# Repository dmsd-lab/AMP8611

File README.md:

### AMP8611 - Integrated class AB Stereo Power Amplifier

Open hardware project under CERN-OHL-S v2 license
 
Amplifier combining a 2-channel input selector, 
PGA2311 digital volume control and 45W per-channel LM3886 output stages.  

Full documentation (description pdf, Kicad project schematic and PCB, Gerber files, BOM, STM32 firmware) is available in the repository.

**Key Specifications**:
- Input resistance: 10kΩ;  
- Nominal input voltage: 0.85Vrms; 
- Maximum output power: 2 x 45W RMS (1kHz sinusoidal, 4ohm load);  
- Bandwidth (-3dB): 20Hz – 90kHz;  
- Volume control: -80 to +12dB;  
- Dimensions: 240 x 265 x 65 mm (80 mm including feet).

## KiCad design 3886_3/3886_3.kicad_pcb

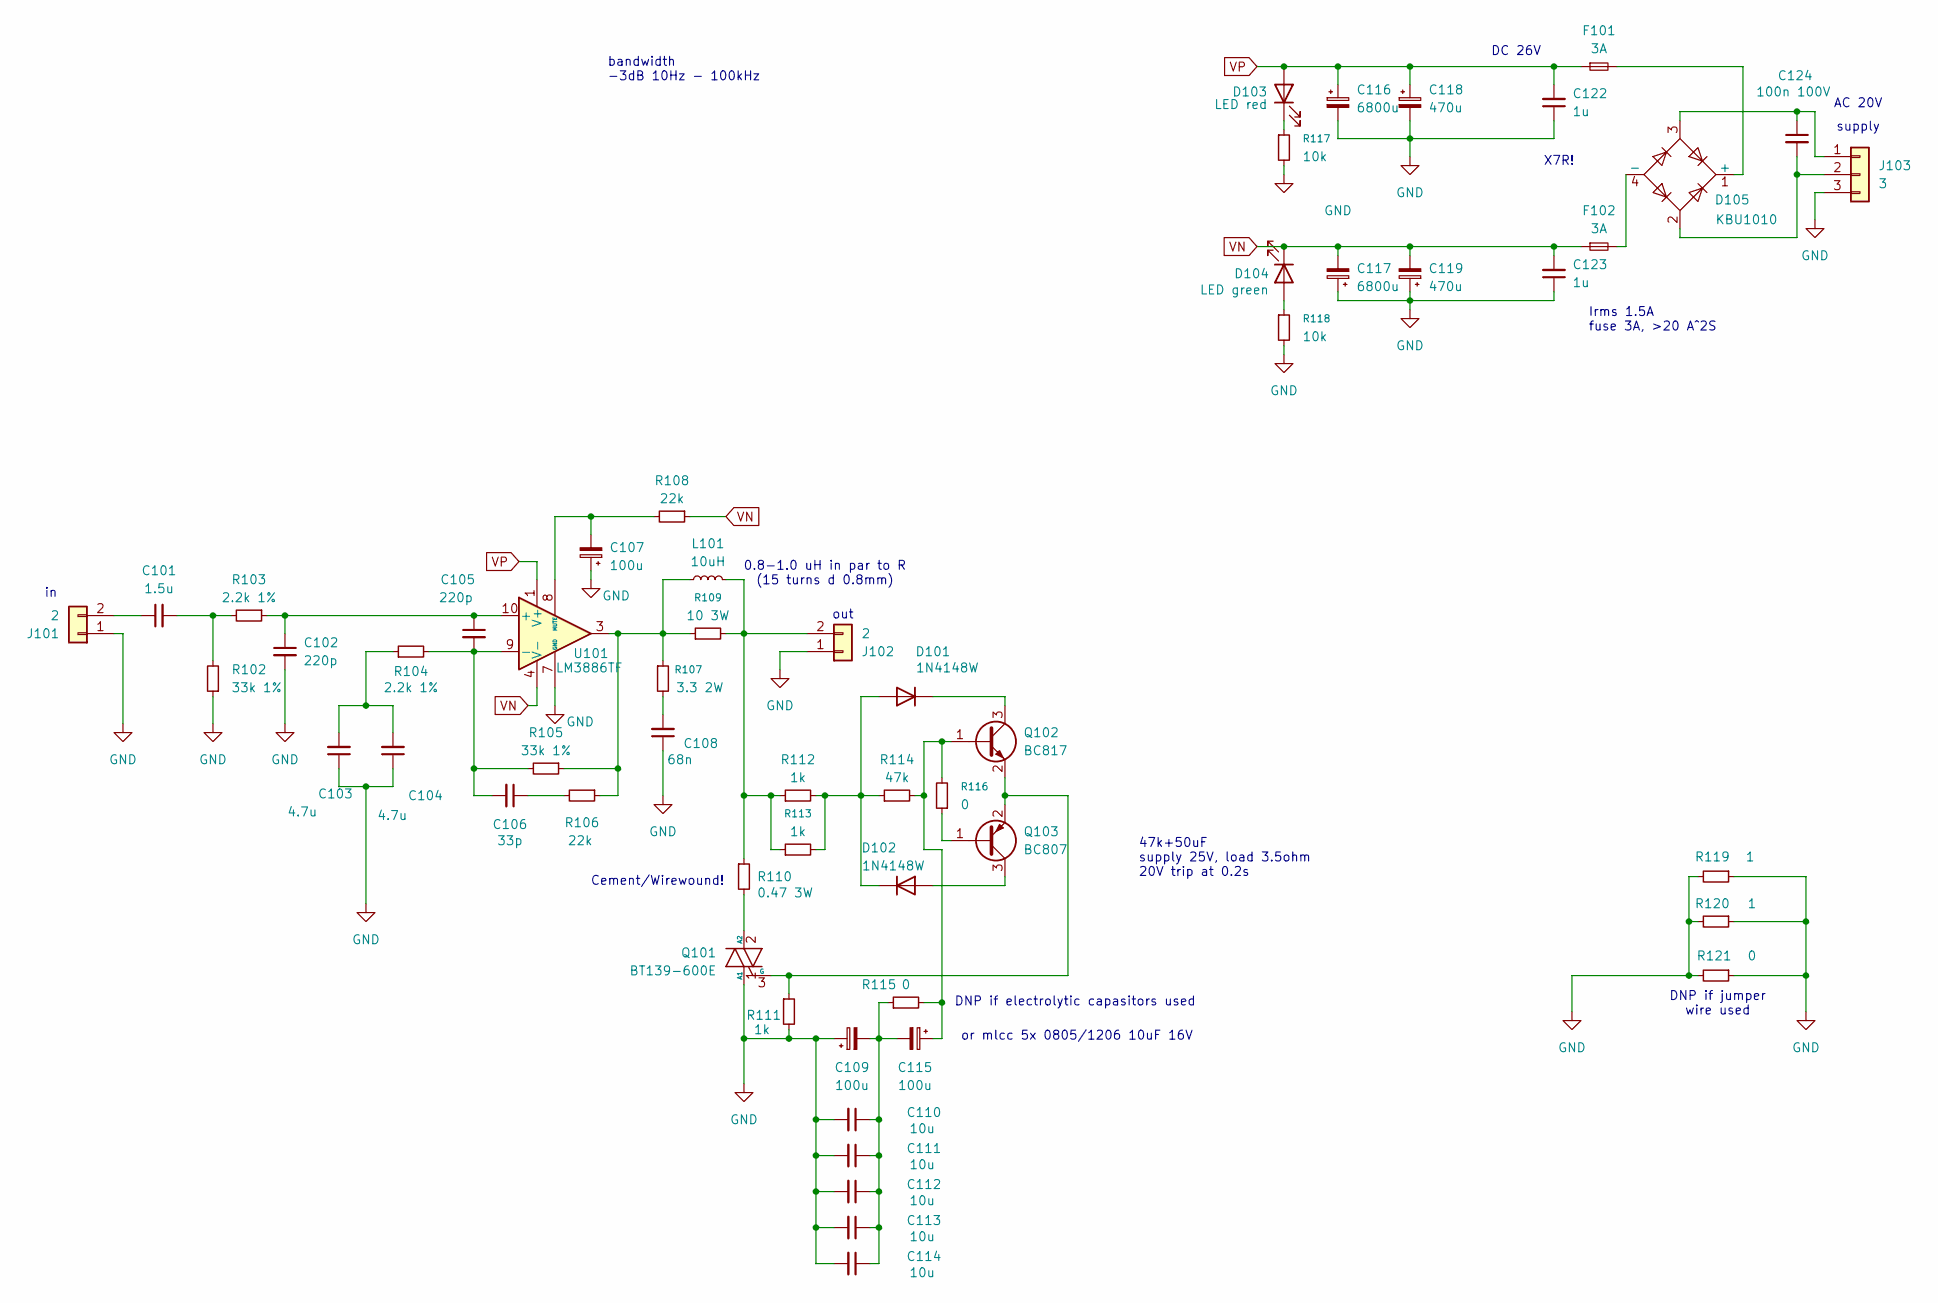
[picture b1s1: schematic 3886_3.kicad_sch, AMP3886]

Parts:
C101: 1.5u; C_Rect_L7.5mm_W6.5mm_P5.00mm
C102: 220p; C_1206_3216Metric_Pad1.33x1.80mm_HandSolder
C103, C104: 4.7u; C_Rect_L31.5mm_W13.0mm_P27.50mm_MKS4
C105: 220p; C_Rect_L7.0mm_W2.5mm_P5.00mm
C106: 33p; C_1206_3216Metric_Pad1.33x1.80mm_HandSolder
C107, C109, C115: 100u; CP_Radial_D6.3mm_P2.50mm
C108: 68n; C_Rect_L7.0mm_W3.5mm_P5.00mm
C110, C111, C112, C113, C114: 10u; C_1206_3216Metric_Pad1.33x1.80mm_HandSolder
C116, C117: 6800u; CP_Radial_D18.0mm_P7.50mm
C118, C119: 470u; CP_Radial_D10.0mm_P5.00mm
C122, C123: 1u; C_1206_3216Metric_Pad1.33x1.80mm_HandSolder
C124: 100n 100V; C_1206_3216Metric_Pad1.33x1.80mm_HandSolder
D101, D102: 1N4148W; D_MELF-RM10_Universal_Handsoldering
D103: LED red; LED_D5.0mm
D104: LED green; LED_D5.0mm
D105: KBU1010; Diode_Bridge_Vishay_KBU
F101, F102: 3A; Fuseholder_Cylinder-5x20mm_Stelvio-Kontek_PTF78_Horizontal_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
J101, J102: 2; PhoenixContact_MCV_1,5_2-G-3.81_1x02_P3.81mm_Vertical
J103: 3; PhoenixContact_MCV_1,5_3-G-5.08_1x03_P5.08mm_Vertical
L101: 10uH
Q101: BT139-600E; TO-220-3_Vertical
Q102: BC817; SOT-23_Handsoldering
Q103: BC807; SOT-23_Handsoldering
R102, R105: 33k 1%; R_Axial_DIN0207_L6.3mm_D2.5mm_P10.16mm_Horizontal
R103, R104: 2.2k 1%; R_Axial_DIN0207_L6.3mm_D2.5mm_P10.16mm_Horizontal
R106, R108: 22k; R_1206_3216Metric_Pad1.30x1.75mm_HandSolder
R107: 3.3 2W; R_Axial_DIN0614_L14.3mm_D5.7mm_P25.40mm_Horizontal
R109: 10 3W; R_Axial_DIN0922_L20.0mm_D9.0mm_P30.48mm_Horizontal
R110: 0.47 3W; R_Axial_Power_L25.0mm_W9.0mm_P7.62mm_Vertical
R111, R112, R113: 1k; R_1206_3216Metric_Pad1.30x1.75mm_HandSolder
R114: 47k; R_1206_3216Metric_Pad1.30x1.75mm_HandSolder
R115, R116: 0; R_1206_3216Metric_Pad1.30x1.75mm_HandSolder
R117, R118: 10k; R_1206_3216Metric_Pad1.30x1.75mm_HandSolder
R119, R120: 1; R_1206_3216Metric_Pad1.30x1.75mm_HandSolder
R121: 0; R_2512_6332Metric_Pad1.40x3.35mm_HandSolder
U101: LM3886TF; TO-220-11_P3.4x5.08mm_StaggerOdd_Lead4.58mm_Vertical

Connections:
GND: C102.2, C103.1, C104.1, C107.1, C108.1, C109.1, C110.2, C111.2, C112.2, C113.2, C114.2, C116.2, C117.1, C118.2, C119.1, C122.1, C123.1, J101.1, J102.1, J103.3, Q101.1 (A1), R102.1, R111.2, R117.2, R118.2, R119.1, R119.2, R120.1, R120.2, R121.1, R121.2, U101.7 (GND)
unnamed: C101.2, R102.2, R103.2
unnamed: C103.2, C104.2, R104.1
unnamed: C106.1, R106.2
unnamed: C108.2, R107.2
unnamed: C109.2, C110.1, C111.1, C112.1, C113.1, C114.1, C115.2, R115.1
unnamed: D101.2 (A), D102.1 (K), R112.2, R113.2, R114.1
unnamed: D101.1 (K), Q102.3 (C)
unnamed: D102.2 (A), Q103.3 (C)
unnamed: D103.1 (K), R117.1
unnamed: D104.2 (A), R118.1
unnamed: D105.1 (+), F101.2
unnamed: D105.4 (-), F102.2
unnamed: C101.1, J101.2
unnamed: J102.2, L101.2, R109.2, R110.1, R112.1, R113.1
unnamed: C124.1, D105.3, J103.1
unnamed: C124.2, D105.2, J103.2
unnamed: Q101.2 (A2), R110.2
unnamed: Q101.3 (G), Q102.2 (E), Q103.2 (E), R111.1
unnamed: C115.1, Q102.1 (B), R114.2, R115.2, R116.2
unnamed: Q103.1 (B), R116.1
unnamed: L101.1, R105.1, R106.1, R107.1, R109.1, U101.3
unnamed: C102.1, C105.1, R103.1, U101.10 (+)
unnamed: C105.2, C106.2, R104.2, R105.2, U101.9 (-)
unnamed: C107.2, R108.2, U101.8 (MUTE)
VN: C117.2, C119.2, C123.2, D104.1 (K), F102.1, R108.1, U101.4 (V-)
VP: C116.1, C118.1, C122.2, D103.2 (A), F101.1, U101.1 (V+), U101.5 (V+)

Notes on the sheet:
DC 26V
supply
X7R!
bandwidth -3dB 10Hz - 100kHz
47k+50uF supply 25V, load 3.5ohm 20V trip at 0.2s
DNP if electrolytic capasitors used
or mlcc 5x 0805/1206 10uF 16V
Irms 1.5A fuse 3A, >20 A^2S
AC 20V
out
0.8-1.0 uH in par to R (15 turns d 0.8mm)
Cement/Wirewound!
DNP if jumper wire used

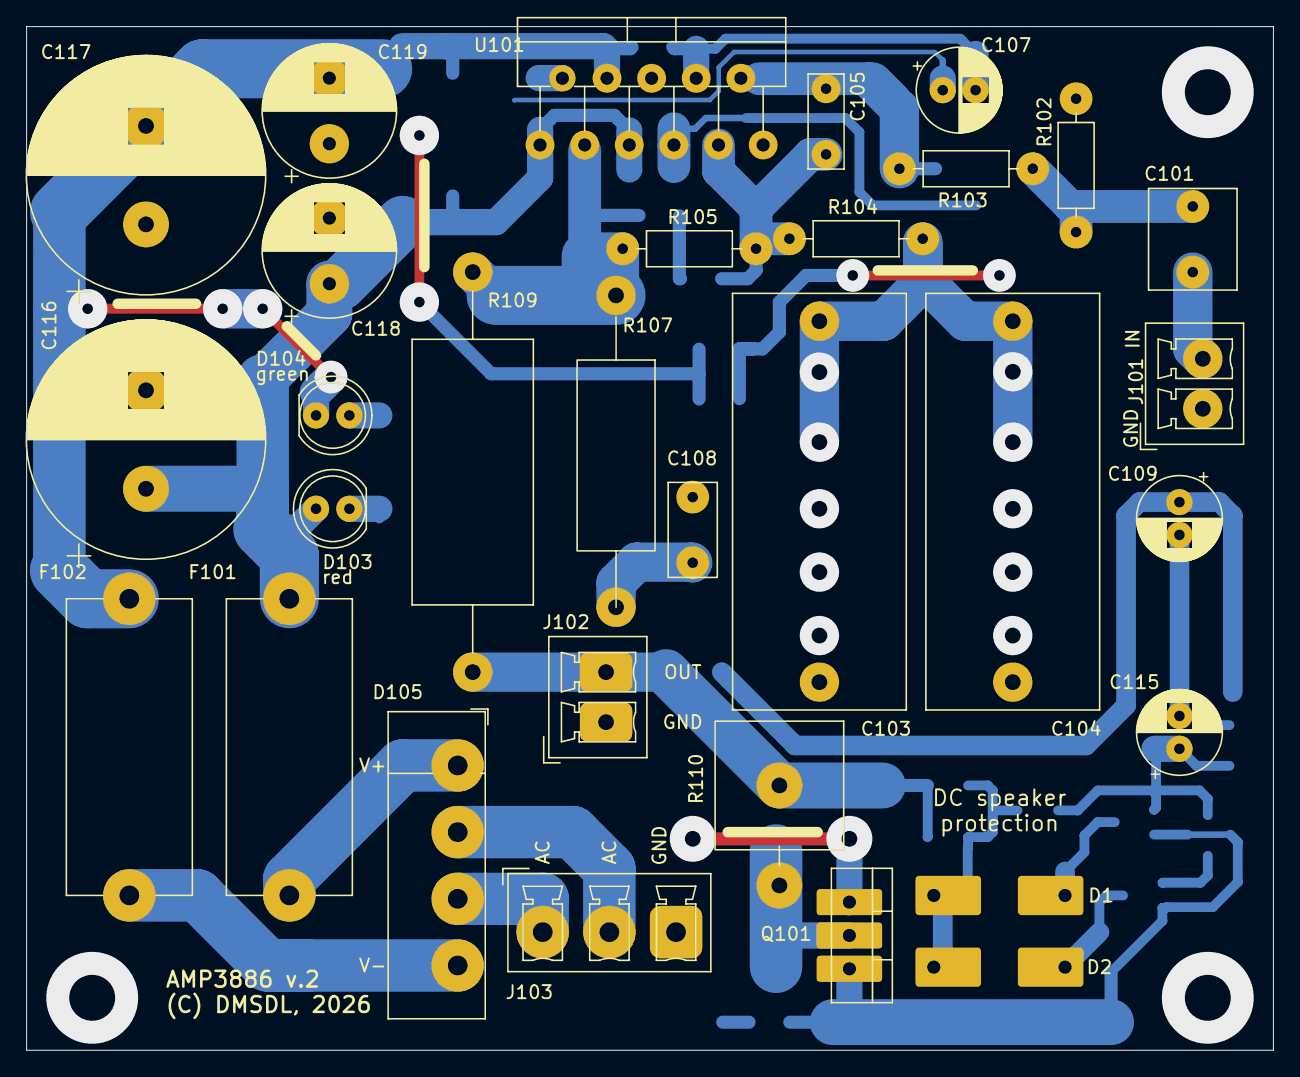
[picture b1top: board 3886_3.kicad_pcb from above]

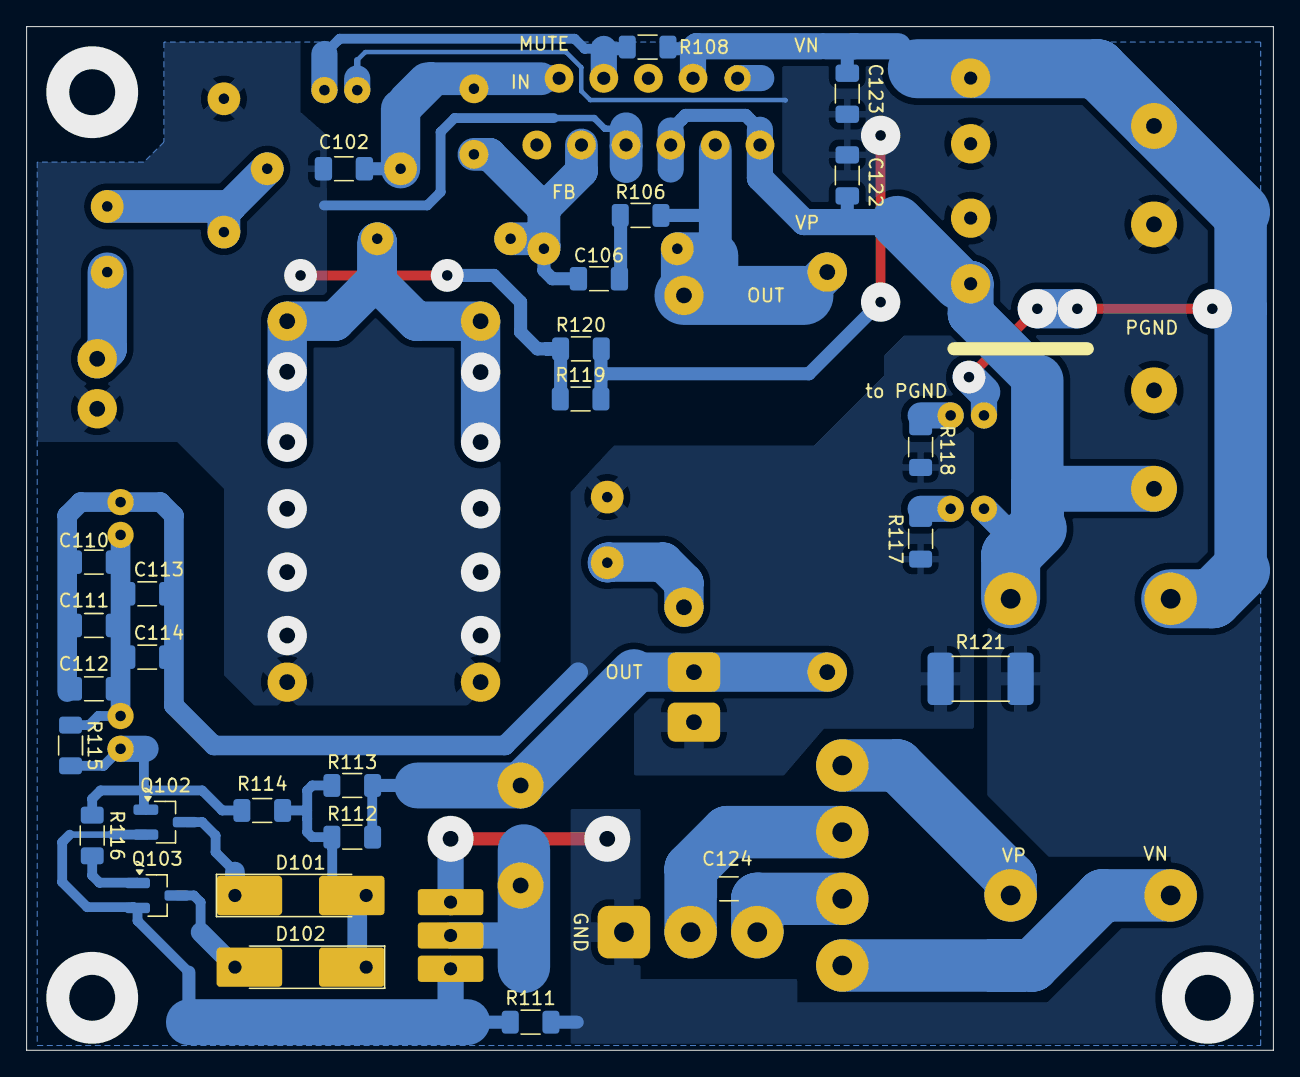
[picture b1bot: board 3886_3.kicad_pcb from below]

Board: 2 copper layers, 95.0 x 78.0 mm, 56 parts (27 on the bottom side), 27 nets.

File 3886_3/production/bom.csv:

Designator,Footprint,Quantity,Value,LCSC Part #
C101,C_Rect_L7.5mm_W6.5mm_P5.00mm,1,1.5u,
C102,1206,1,220p,
"C103, C104",C_Rect_L31.5mm_W13.0mm_P27.50mm_MKS4,2,4.7u,
C105,C_Rect_L7.0mm_W2.5mm_P5.00mm,1,220p,
C106,1206,1,33p,
"C107, C109, C115",CP_Radial_D6.3mm_P2.50mm,3,100u,
C108,C_Rect_L7.0mm_W3.5mm_P5.00mm,1,68n,
"C110, C111, C112, C113, C114",1206,5,10u,
"C116, C117",CP_Radial_D18.0mm_P7.50mm,2,6800u,
"C118, C119",CP_Radial_D10.0mm_P5.00mm,2,470u,
"C122, C123",1206,2,1u,
C124,1206,1,100n 100V,
"D101, D102",D_MELF-RM10_Universal_Handsoldering,2,1N4148W,
D103,LED_D5.0mm,1,LED red,
D104,LED_D5.0mm,1,LED green,
D105,Diode_Bridge_Vishay_KBU,1,KBU1010,
"F101, F102",Fuseholder_Cylinder-5x20mm_Stelvio-Kontek_PTF78_Horizontal_Open,2,3A,
"J101, J102","PhoenixContact_MCV_1,5_2-G-3.81_1x02_P3.81mm_Vertical",2,2,
J103,"PhoenixContact_MCV_1,5_3-G-5.08_1x03_P5.08mm_Vertical",1,3,
Q101,TO-220-3_Vertical,1,BT139-600E,
Q102,SOT-23_Handsoldering,1,BC817,
Q103,SOT-23_Handsoldering,1,BC807,
"R102, R105",R_Axial_DIN0207_L6.3mm_D2.5mm_P10.16mm_Horizontal,2,33k 1%,
"R103, R104",R_Axial_DIN0207_L6.3mm_D2.5mm_P10.16mm_Horizontal,2,2.2k 1%,
"R106, R108",1206,2,22k,
R107,R_Axial_DIN0614_L14.3mm_D5.7mm_P25.40mm_Horizontal,1,3.3 2W,
R109,R_Axial_DIN0922_L20.0mm_D9.0mm_P30.48mm_Horizontal,1,10 3W,
R110,R_Axial_Power_L25.0mm_W9.0mm_P7.62mm_Vertical,1,0.47 3W,
"R111, R112, R113",1206,3,1k,
R114,1206,1,47k,
"R115, R116",1206,2,0,
"R117, R118",1206,2,10k,
"R119, R120",1206,2,1,
R121,2512,1,0,
U101,TO-220-11_P3.4x5.08mm_StaggerOdd_Lead4.58mm_Vertical,1,LM3886TF,

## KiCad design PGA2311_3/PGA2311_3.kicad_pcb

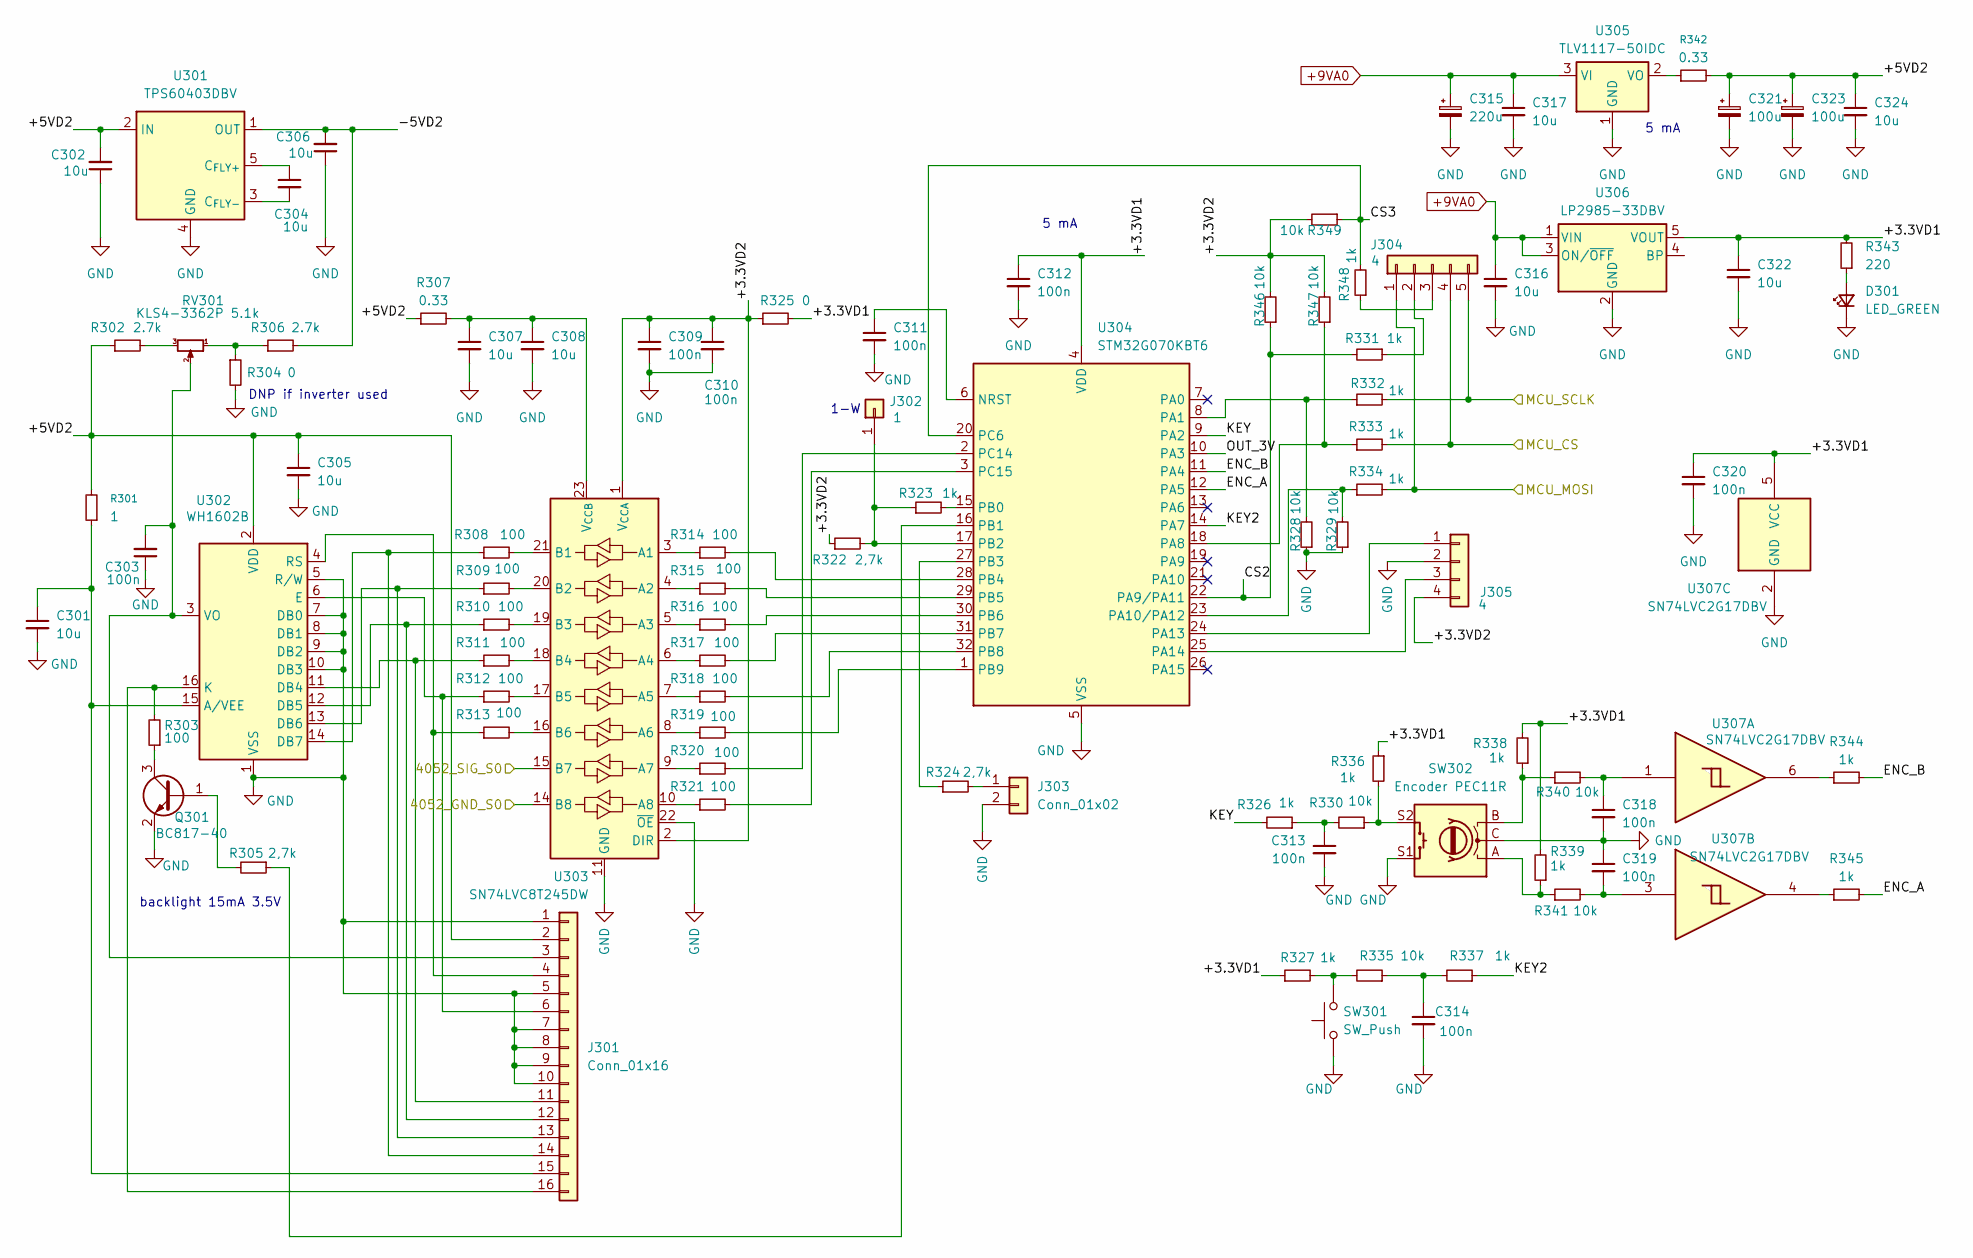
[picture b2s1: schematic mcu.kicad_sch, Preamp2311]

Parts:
C301, C302, C304, C305, C306, C307, C308, C316, C317, C322, C324: 10u; C_0805_2012Metric_Pad1.18x1.45mm_HandSolder
C303, C309, C310, C311, C312, C313, C314, C318, C319, C320: 100n; C_0805_2012Metric_Pad1.18x1.45mm_HandSolder
C315: 220u; CP_Radial_D8.0mm_P3.50mm
C321, C323: 100u; CP_Radial_D6.3mm_P2.50mm
D301: LED_GREEN; LED_D3.0mm
J301: Conn_01x16; PinSocket_1x16_P2.54mm_Horizontal
J302: 1; PinHeader_1x01_P2.54mm_Vertical
J303: Conn_01x02; PinHeader_1x02_P2.54mm_Vertical
J304: 4; PinHeader_1x05_P2.54mm_Vertical
J305: 4; PinHeader_1x04_P2.54mm_Vertical
Q301: BC817-40; SOT-23_Handsoldering
R301: 1; R_1206_3216Metric_Pad1.30x1.75mm_HandSolder
R302, R306: 2.7k; R_0805_2012Metric_Pad1.20x1.40mm_HandSolder
R303: 100; R_1206_3216Metric_Pad1.30x1.75mm_HandSolder
R304, R325: 0; R_0805_2012Metric_Pad1.20x1.40mm_HandSolder
R305, R322, R324: 2,7k; R_0805_2012Metric_Pad1.20x1.40mm_HandSolder
R307, R342: 0.33; R_0805_2012Metric_Pad1.20x1.40mm_HandSolder
R308, R309, R310, R311, R312, R313, R314, R315, R316, R317, R318, R319, R320, R321: 100; R_0805_2012Metric_Pad1.20x1.40mm_HandSolder
R323, R326, R327, R331, R332, R333, R334, R336, R337, R338, R339, R344, R345, R348: 1k; R_0805_2012Metric_Pad1.20x1.40mm_HandSolder
R328, R329, R330, R335, R340, R341, R346, R347, R349: 10k; R_0805_2012Metric_Pad1.20x1.40mm_HandSolder
R343: 220; R_0805_2012Metric_Pad1.20x1.40mm_HandSolder
RV301: KLS4-3362P 5.1k; Potentiometer_Vishay_T73YP_Vertical
SW301: SW_Push; SW_PUSH-12mm
SW302: Encoder PEC11R; RotaryEncoder_Alps_EC12E-Switch_Vertical_H20mm_CircularMoun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
U301: TPS60403DBV; SOT-23-5_HandSoldering
U302: WH1602B; WC1602A
U303: SN74LVC8T245DW; SOIC-24W_7.5x15.4mm_P1.27mm
U304: STM32G070KBT6; LQFP-32_7x7mm_P0.8mm
U305: TLV1117-50IDC; SOT-223-3_TabPin2
U306: LP2985-33DBV; SOT-23-5_HandSoldering
U307: SN74LVC2G17DBV; SOT-23-6_Handsoldering

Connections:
+9VA0: C315.1, C316.1, C317.1, U305.3 (VI), U306.1 (VIN), U306.3 (ON/~OFF); also elsewhere on the board
/analog/4052_GND_S0: U303.14 (B8); also elsewhere on the board
/analog/4052_SIG_S0: U303.15 (B7); also elsewhere on the board
/analog/MCU_CS: J304.4, R333.2; also elsewhere on the board
/analog/MCU_MOSI: J304.1, R334.2; also elsewhere on the board
/analog/MCU_SCLK: J304.5, R332.2; also elsewhere on the board
/mcu/+3.3VD1: C312.1, C320.1, C322.1, R325.2, R327.1, R336.1, R338.2, R339.2, R343.2, U304.4 (VDD), U306.5 (VOUT), U307.5 (VCC)
/mcu/+3.3VD2: C309.1, C310.1, J305.4, R322.1, R325.1, R346.2, R347.2, R349.2, U303.1 (V_{CCA}), U303.2 (DIR)
/mcu/+5VD2: C302.2, C305.1, C321.1, C323.1, C324.1, J301.2, R301.2, R302.1, R307.1, R342.2, U301.2 (IN), U302.2 (VDD)
/mcu/-5VD2: C306.2, R306.2, U301.1 (OUT)
/mcu/CS2: R331.2, R346.1, U304.22 (PA9/PA11)
/mcu/CS3: R348.2, R349.1, U304.20 (PC6)
/mcu/ENC_A: R345.2, U304.12 (PA5)
/mcu/ENC_B: R344.2, U304.11 (PA4)
/mcu/KEY: R326.2, U304.9 (PA2)
/mcu/KEY2: R337.1, U304.14 (PA7)
/mcu/OUT_3V: U304.10 (PA3)
GND: C301.2, C302.1, C303.1, C305.2, C306.1, C307.2, C308.2, C309.2, C310.2, C311.2, C312.2, C313.2, C314.2, C315.2, C316.2, C317.2, C318.2, C319.1, C320.2, C321.2, C322.2, C323.2, C324.2, D301.1 (K), J301.1, J301.5, J301.7, J301.8, J301.9, J301.10, J303.2, J305.2, Q301.2 (E), R304.2, R328.1, R329.1, SW301.1, SW302.C, SW302.S1, U301.4 (GND), U302.1 (VSS), U302.5 (R/W), U302.7 (DB0), U302.8 (DB1), U302.9 (DB2), U302.10 (DB3), U303.11 (GND), U303.12 (GND), U303.13 (GND), U303.22 (~OE), U304.5 (VSS), U305.1 (GND), U306.2 (GND), U307.2 (GND); also elsewhere on the board
unnamed: C307.1, C308.1, R307.2, U303.23 (V_{CCB}), U303.24 (V_{CCB})
unnamed: C313.1, R326.1, R330.2
unnamed: C314.1, R335.1, R337.2
unnamed: C318.1, R340.2, U307.1
unnamed: C319.2, R341.2, U307.3
unnamed: D301.2 (A), R343.1
unnamed: C303.2, J301.3, RV301.2, U302.3 (VO)
unnamed: J301.4, R313.1, U302.4 (RS)
unnamed: J301.6, R312.1, U302.6 (E)
unnamed: J301.11, R311.1, U302.11 (DB4)
unnamed: J301.12, R310.1, U302.12 (DB5)
unnamed: J301.13, R309.1, U302.13 (DB6)
unnamed: J301.14, R308.1, U302.14 (DB7)
unnamed: C301.1, J301.15, R301.1, U302.15 (A/VEE)
unnamed: J301.16, R303.2, U302.16 (K)
unnamed: J302.1, R322.2, R323.1, U304.17 (PB2)
unnamed: J303.1, R324.2
unnamed: J304.2, R331.1
unnamed: J304.3, R348.1
unnamed: J305.1, U304.24 (PA13)
unnamed: J305.3, U304.25 (PA14)
unnamed: Q301.1 (B), R305.2
unnamed: Q301.3 (C), R303.1
unnamed: R302.2, RV301.3
unnamed: R304.1, R306.1, RV301.1
unnamed: R327.2, R335.2, SW301.2
unnamed: R330.1, R336.2, SW302.S2
unnamed: R338.1, R340.1, SW302.B
unnamed: R339.1, R341.1, SW302.A
unnamed: R344.1, U307.6
unnamed: R345.1, U307.4
unnamed: C304.1, U301.5 (C_{FLY+})
unnamed: C304.2, U301.3 (C_{FLY-})
unnamed: R314.1, U303.3 (A1)
unnamed: R315.1, U303.4 (A2)
unnamed: R316.1, U303.5 (A3)
unnamed: R317.1, U303.6 (A4)
unnamed: R318.1, U303.7 (A5)
unnamed: R319.1, U303.8 (A6)
unnamed: R320.1, U303.9 (A7)
unnamed: R321.1, U303.10 (A8)
unnamed: R308.2, U303.21 (B1)
unnamed: R309.2, U303.20 (B2)
unnamed: R310.2, U303.19 (B3)
unnamed: R311.2, U303.18 (B4)
unnamed: R312.2, U303.17 (B5)
unnamed: R313.2, U303.16 (B6)
unnamed: C311.1, U304.6 (NRST)
unnamed: R328.2, R332.1, U304.8 (PA1)
unnamed: R333.1, R347.1, U304.18 (PA8)
unnamed: R329.2, R334.1, U304.23 (PA10/PA12)
unnamed: R323.2, U304.15 (PB0)
unnamed: R305.1, U304.16 (PB1)
unnamed: R324.1, U304.27 (PB3)
unnamed: R314.2, U304.28 (PB4)
unnamed: R315.2, U304.29 (PB5)
unnamed: R316.2, U304.30 (PB6)
unnamed: R317.2, U304.31 (PB7)
unnamed: R318.2, U304.32 (PB8)
unnamed: R319.2, U304.1 (PB9)
unnamed: R320.2, U304.2 (PC14)
unnamed: R321.2, U304.3 (PC15)
unnamed: R342.1, U305.2 (VO)

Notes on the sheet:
5 mA
DNP if inverter used
1-W
backlight 15mA 3.5V

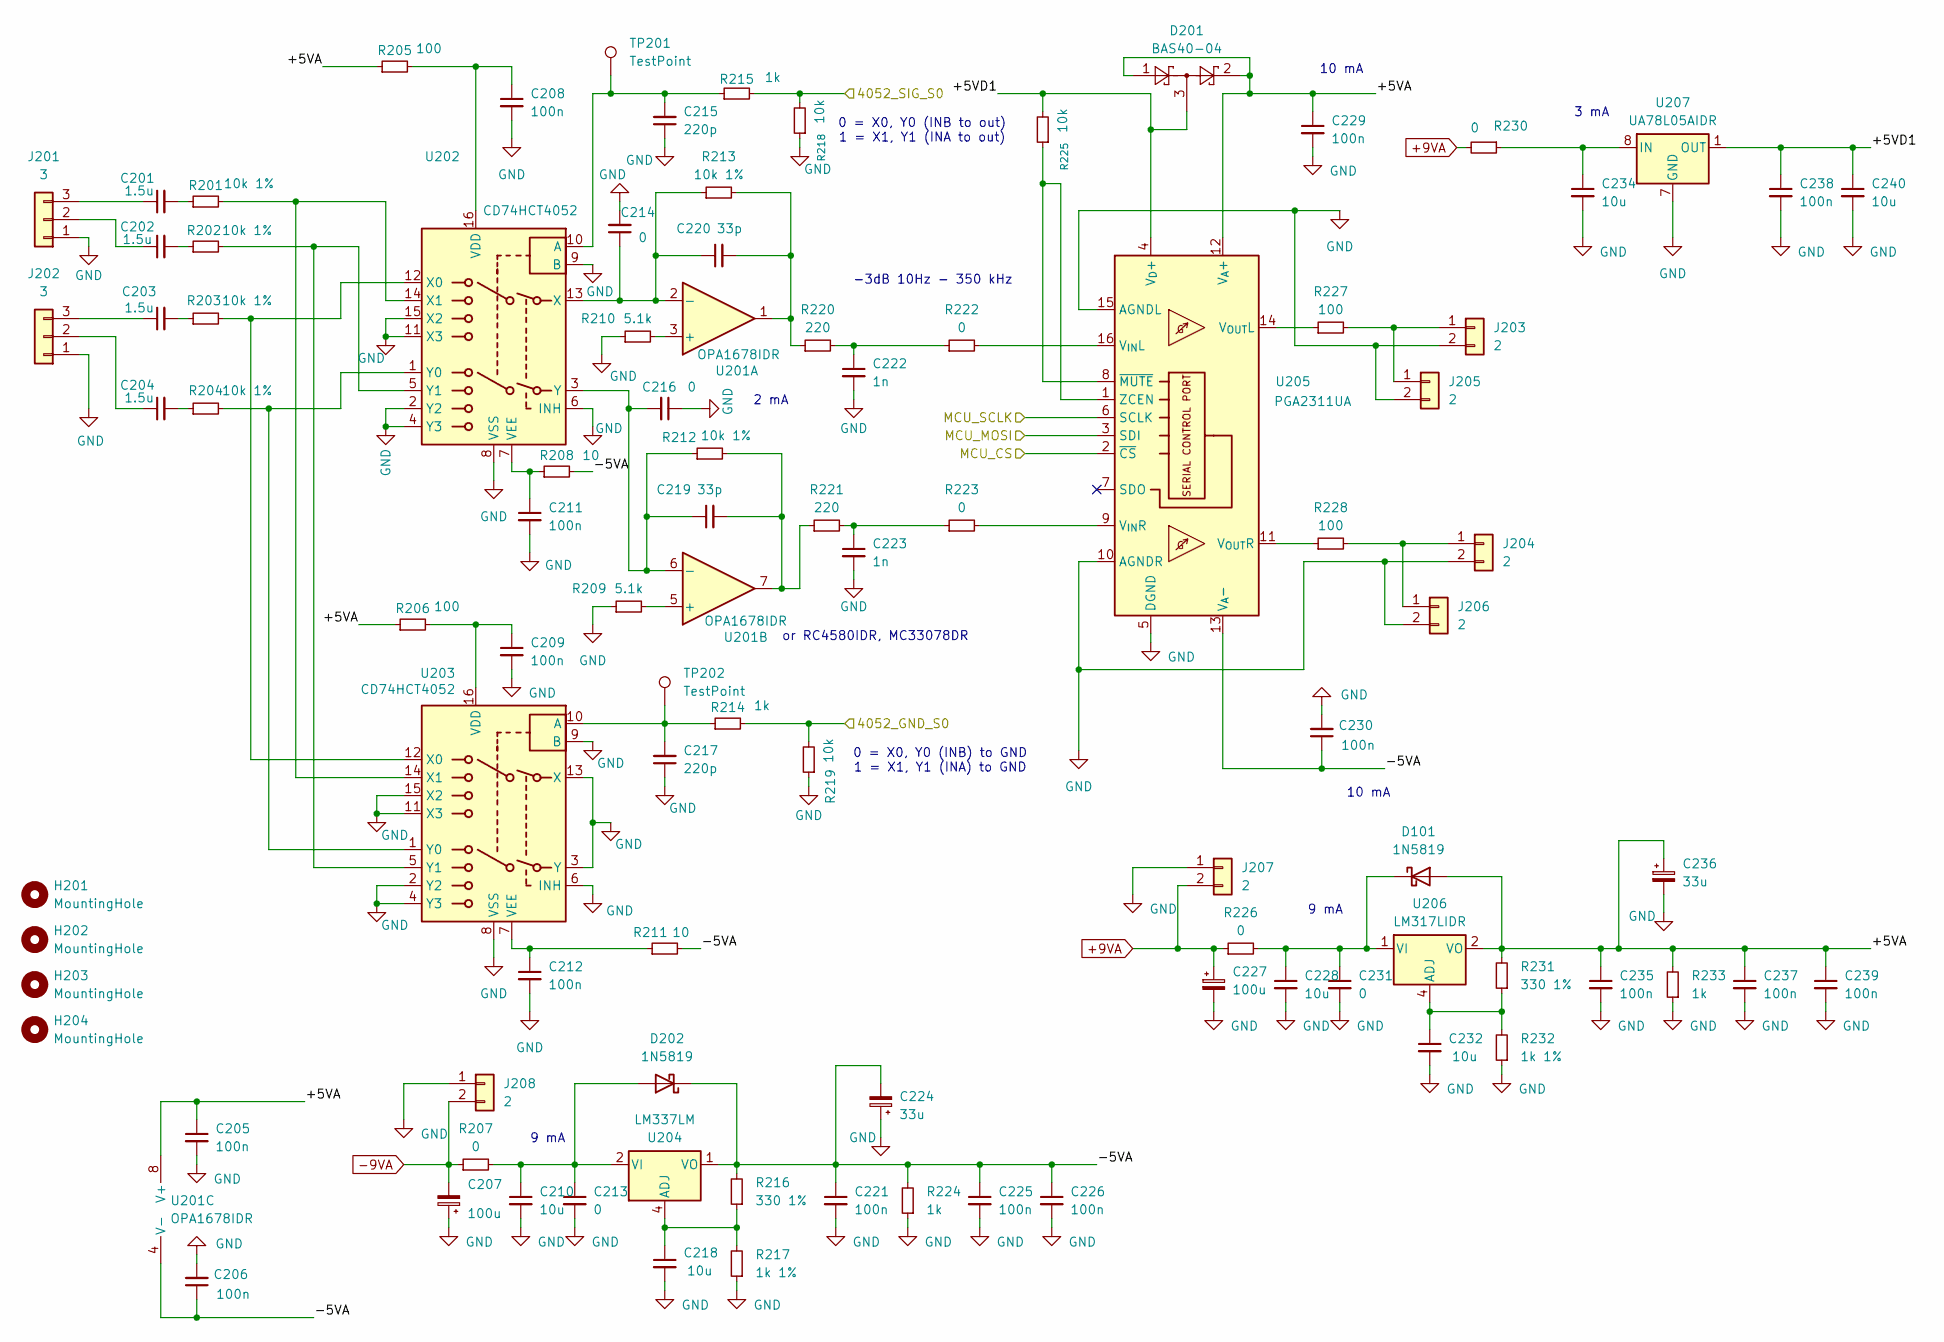
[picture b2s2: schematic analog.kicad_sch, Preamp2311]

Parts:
C201, C202, C203, C204: 1.5u; C_Rect_L7.2mm_W7.2mm_P5.00mm_FKS2_FKP2_MKS2_MKP2
C205, C206, C208, C209, C211, C212, C221, C225, C226, C229, C230, C235, C237, C238, C239: 100n; C_0805_2012Metric_Pad1.18x1.45mm_HandSolder
C207, C227: 100u; CP_Radial_D6.3mm_P2.50mm
C210, C218, C228, C232, C234, C240: 10u; C_0805_2012Metric_Pad1.18x1.45mm_HandSolder
C213, C214, C216, C231: 0; C_0805_2012Metric_Pad1.18x1.45mm_HandSolder
C215, C217: 220p; C_0805_2012Metric_Pad1.18x1.45mm_HandSolder
C219, C220: 33p; C_0805_2012Metric_Pad1.18x1.45mm_HandSolder
C222, C223: 1n; C_0805_2012Metric_Pad1.18x1.45mm_HandSolder
C224, C236: 33u; CP_EIA-6032-20_AVX-F_HandSolder
D101, D202: 1N5819; D_SOD-123
D201: BAS40-04; SOT-23_Handsoldering
H201, H202, H203, H204: MountingHole; MountingHole_2.7mm_M2.5
J201, J202: 3; PhoenixContact_MCV_1,5_3-G-3.81_1x03_P3.81mm_Vertical
J203, J204: 2; PhoenixContact_MCV_1,5_2-G-3.81_1x02_P3.81mm_Vertical
J205, J206, J207, J208: 2; PinHeader_1x02_P2.54mm_Vertical
R201, R202, R203, R204, R212, R213: 10k 1%; R_1206_3216Metric_Pad1.30x1.75mm_HandSolder
R205, R206, R227, R228: 100; R_0805_2012Metric_Pad1.20x1.40mm_HandSolder
R207, R222, R223, R226, R230: 0; R_0805_2012Metric_Pad1.20x1.40mm_HandSolder
R208, R211: 10; R_0805_2012Metric_Pad1.20x1.40mm_HandSolder
R209, R210: 5.1k; R_0805_2012Metric_Pad1.20x1.40mm_HandSolder
R214, R215, R224, R233: 1k; R_0805_2012Metric_Pad1.20x1.40mm_HandSolder
R216, R231: 330 1%; R_0805_2012Metric_Pad1.20x1.40mm_HandSolder
R217, R232: 1k 1%; R_0805_2012Metric_Pad1.20x1.40mm_HandSolder
R218, R219, R225: 10k; R_0805_2012Metric_Pad1.20x1.40mm_HandSolder
R220, R221: 220; R_0805_2012Metric_Pad1.20x1.40mm_HandSolder
TP201, TP202: TestPoint; TestPoint_THTPad_2.0x2.0mm_Drill1.0mm
U201: OPA1678IDR; SOIC-8_3.9x4.9mm_P1.27mm
U202, U203: CD74HCT4052; SOIC-16_3.9x9.9mm_P1.27mm
U204: LM337LM; SOIC-8_3.9x4.9mm_P1.27mm
U205: PGA2311UA; SOIC-16W_7.5x10.3mm_P1.27mm
U206: LM317LIDR; SOIC-8_3.9x4.9mm_P1.27mm
U207: UA78L05AIDR; SOIC-8_3.9x4.9mm_P1.27mm

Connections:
+9VA: C227.1, J207.2, R226.1, R230.2; also elsewhere on the board
-9VA: C207.2, J208.2, R207.1; also elsewhere on the board
/analog/4052_GND_S0: R214.2, R219.2; also elsewhere on the board
/analog/4052_SIG_S0: R215.2, R218.2; also elsewhere on the board
/analog/+5VA: C205.1, C229.1, C235.1, C236.1, C237.1, C239.1, D101.2 (A), D201.1, D201.2, R205.1, R206.1, R231.2, R233.2, U201.8 (V+), U205.12 (V_{A}+), U206.2 (VO), U206.3 (VO), U206.6 (VO), U206.7 (VO)
/analog/+5VD1: C238.1, C240.1, D201.3, R225.2, U205.4 (V_{D}+), U207.1 (OUT)
/analog/-5VA: C206.1, C221.1, C224.2, C225.1, C226.1, C230.1, D202.1 (K), R208.2, R211.2, R216.2, R224.2, U201.4 (V-), U204.1 (VO), U205.13 (V_{A}-)
/analog/MCU_CS: U205.2 (~CS); also elsewhere on the board
/analog/MCU_MOSI: U205.3 (SDI); also elsewhere on the board
/analog/MCU_SCLK: U205.6 (SCLK); also elsewhere on the board
GND: C205.2, C206.2, C207.1, C208.2, C209.2, C210.2, C211.2, C212.2, C213.2, C214.2, C215.1, C216.1, C217.1, C218.2, C221.2, C222.2, C223.2, C224.1, C225.2, C226.2, C227.2, C228.2, C229.2, C230.2, C231.2, C232.2, C234.2, C235.2, C236.2, C237.2, C238.2, C239.2, C240.2, J201.1, J202.1, J203.2, J204.2, J205.2, J206.2, J207.1, J208.1, R209.1, R210.1, R217.1, R218.1, R219.1, R224.1, R232.1, R233.1, U202.2 (Y2), U202.4 (Y3), U202.6 (INH), U202.8 (VSS), U202.9 (B), U202.11 (X3), U202.15 (X2), U203.2 (Y2), U203.3 (Y), U203.4 (Y3), U203.6 (INH), U203.8 (VSS), U203.9 (B), U203.11 (X3), U203.13 (X), U203.15 (X2), U205.5 (DGND), U205.10 (AGNDR), U205.15 (AGNDL), U207.2 (GND), U207.3 (GND), U207.6 (GND), U207.7 (GND); also elsewhere on the board
unnamed: C201.2, R201.1
unnamed: C202.2, R202.1
unnamed: C203.2, R203.1
unnamed: C204.2, R204.1
unnamed: C219.2, R212.2, R221.1, U201.7
unnamed: C220.2, R213.2, R220.1, U201.1
unnamed: C222.1, R220.2, R222.1
unnamed: C223.1, R221.2, R223.1
unnamed: C228.1, C231.1, D101.1 (K), R226.2, U206.1 (VI)
unnamed: C210.1, C213.1, D202.2 (A), R207.2, U204.2 (VI), U204.3 (VI), U204.6 (VI), U204.7 (VI)
unnamed: C202.1, J201.2
unnamed: C201.1, J201.3
unnamed: C204.1, J202.2
unnamed: C203.1, J202.3
unnamed: J203.1, J205.1, R227.2
unnamed: J204.1, J206.1, R228.2
unnamed: R210.2, U201.3 (+)
unnamed: C214.1, C220.1, R213.1, U201.2 (-), U202.13 (X)
unnamed: R209.2, U201.5 (+)
unnamed: C216.2, C219.1, R212.1, U201.6 (-), U202.3 (Y)
unnamed: C215.2, R215.1, TP201.1, U202.10 (A)
unnamed: C208.1, R205.2, U202.16 (VDD)
unnamed: C211.1, R208.1, U202.7 (VEE)
unnamed: R203.2, U202.12 (X0), U203.12 (X0)
unnamed: R201.2, U202.14 (X1), U203.14 (X1)
unnamed: R204.2, U202.1 (Y0), U203.1 (Y0)
unnamed: R202.2, U202.5 (Y1), U203.5 (Y1)
unnamed: C217.2, R214.1, TP202.1, U203.10 (A)
unnamed: C209.1, R206.2, U203.16 (VDD)
unnamed: C212.1, R211.1, U203.7 (VEE)
unnamed: C218.1, R216.1, R217.2, U204.4 (ADJ)
unnamed: R222.2, U205.16 (V_{IN}L)
unnamed: R223.2, U205.9 (V_{IN}R)
unnamed: R227.1, U205.14 (V_{OUT}L)
unnamed: R228.1, U205.11 (V_{OUT}R)
unnamed: R225.1, U205.1 (ZCEN), U205.8 (~MUTE)
unnamed: C232.1, R231.1, R232.2, U206.4 (ADJ)
unnamed: C234.1, R230.1, U207.8 (IN)

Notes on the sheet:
9 mA
3 mA
10 mA
0 = X0, Y0 (INB) to GND 1 = X1, Y1 (INA) to GND
0 = X0, Y0 (INB to out) 1 = X1, Y1 (INA to out)
2 mA
-3dB 10Hz - 350 kHz
or RC4580IDR, MC33078DR

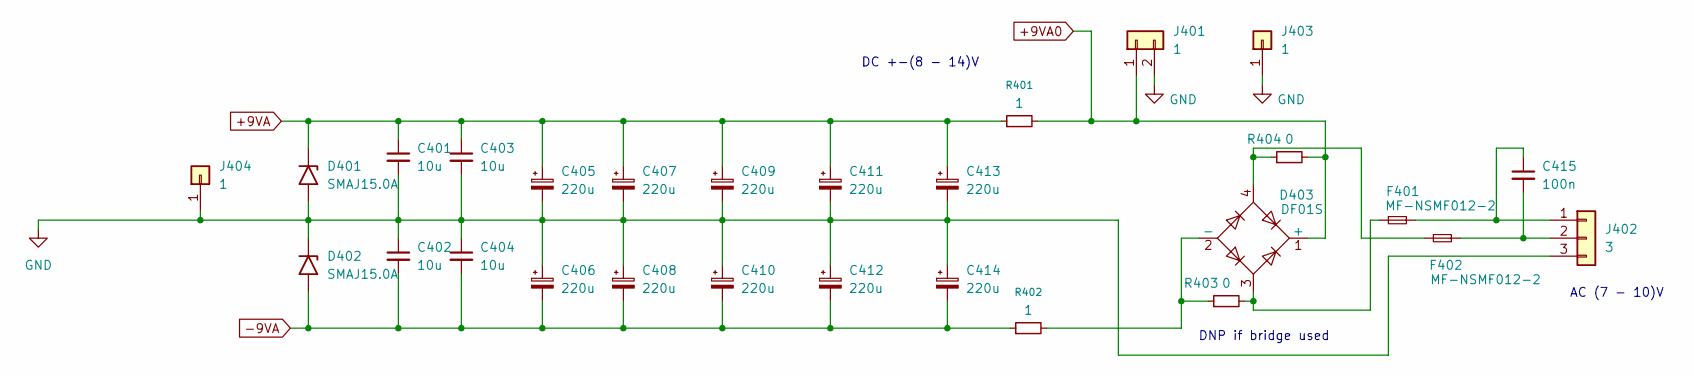
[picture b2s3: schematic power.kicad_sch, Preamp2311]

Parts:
C401, C402, C403, C404: 10u; C_0805_2012Metric_Pad1.18x1.45mm_HandSolder
C405, C406, C407, C408, C409, C410, C411, C412, C413, C414: 220u; CP_Radial_D8.0mm_P3.50mm
C415: 100n; C_1206_3216Metric_Pad1.33x1.80mm_HandSolder
D401, D402: SMAJ15.0A; D_SMB
D403: DF01S; Diode_Bridge_OnSemi_SDIP-4L
F401, F402: MF-NSMF012-2; Fuse_1206_3216Metric
J401: 1; PinHeader_1x02_P2.54mm_Vertical
J402: 3; PhoenixContact_MCV_1,5_3-G-3.81_1x03_P3.81mm_Vertical
J403, J404: 1; PinHeader_1x01_P2.54mm_Vertical
R401, R402: 1; R_1206_3216Metric_Pad1.30x1.75mm_HandSolder
R403, R404: 0; R_1206_3216Metric_Pad1.30x1.75mm_HandSolder

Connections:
+9VA: C401.1, C403.1, C405.1, C407.1, C409.1, C411.1, C413.1, D401.1 (A1), R401.1; also elsewhere on the board
+9VA0: D403.1 (+), J401.1, R401.2, R404.2; also elsewhere on the board
-9VA: C402.2, C404.2, C406.2, C408.2, C410.2, C412.2, C414.2, D402.2 (A2), R402.1; also elsewhere on the board
GND: C401.2, C402.1, C403.2, C404.1, C405.2, C406.1, C407.2, C408.1, C409.2, C410.1, C411.2, C412.1, C413.2, C414.1, D401.2 (A2), D402.1 (A1), J401.2, J402.3, J403.1, J404.1; also elsewhere on the board
unnamed: D403.2 (-), R402.2, R403.1
unnamed: D403.3, F401.1, R403.2
unnamed: D403.4, F402.1, R404.1
unnamed: C415.1, F401.2, J402.1
unnamed: C415.2, F402.2, J402.2

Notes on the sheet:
DNP if bridge used
AC (7 - 10)V
DC +-(8 - 14)V
